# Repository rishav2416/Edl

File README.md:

# EDL Project of Group 10, Spring 2020-21
## PCB design
This repository contains all the files such as schematic, Board files needed to manufacture our pcb design. This PCB design is of a Temperature Controller Circuit which controls the temperature of a box in a said range with very less error

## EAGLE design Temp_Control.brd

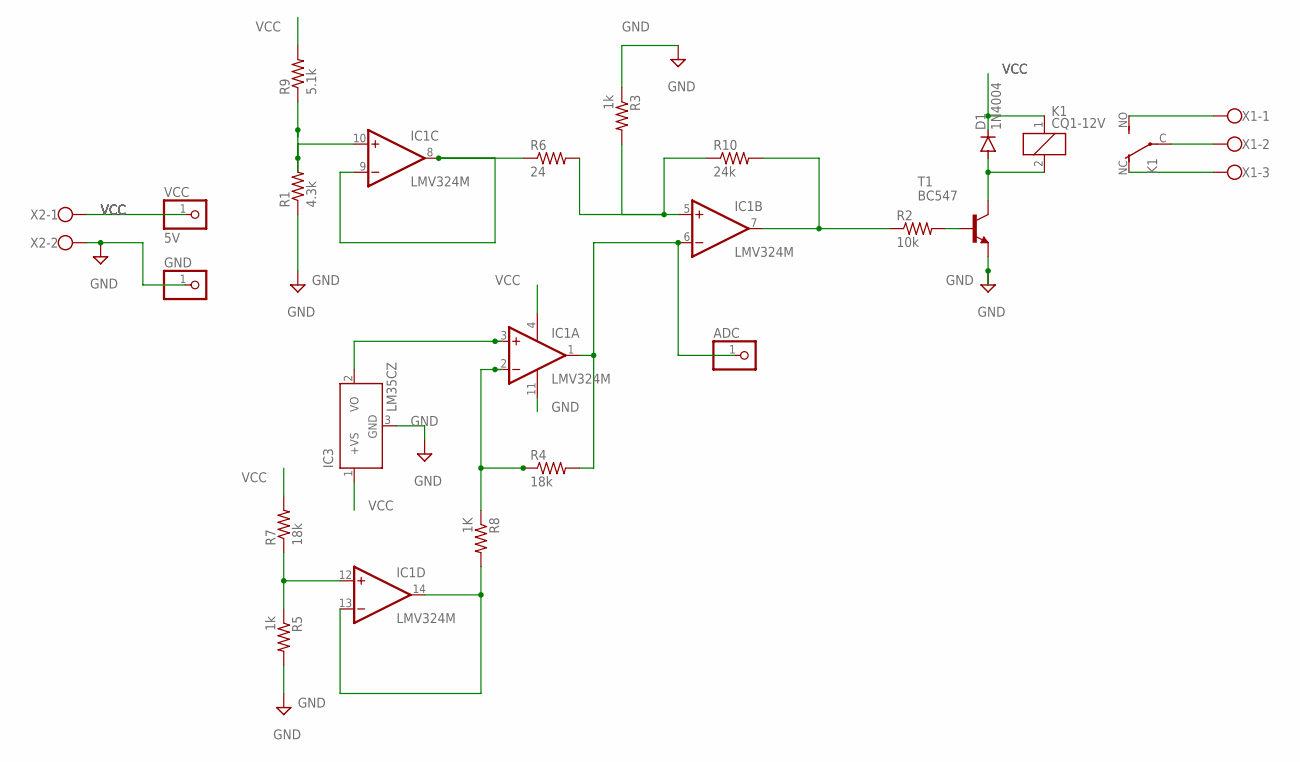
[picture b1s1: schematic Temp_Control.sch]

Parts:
ADC: PINHD-1X1; 1X01
D1: 1N4004; DO41-10
GND: PINHD-1X1; 1X01
IC1: LMV324M; SO14
IC3: LM35CZ; TO92
K1: CQ1-12V; CQ1
R1: 4.3k; 0207/10
R2: 10k; 0207/10
R3, R5: 1k; 0207/10
R4, R7: 18k; 0207/10
R6: 24; 0207/10
R8: 1K; 0207/10
R9: 5.1k; 0207/10
R10: 24k; 0207/10
T1: BC547; TO92
VCC: 5V; 1X01
X1: W237-103
X2: W237-102

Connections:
GND: GND.1, IC1.11 (V-), IC3.3 (GND), R1.1, R3.1, R5.2, T1.1 (E), X2.2
unnamed: IC1.3 (+IN), IC3.2 (VO)
unnamed: IC1.2 (-IN), R4.1, R8.1
unnamed: ADC.1, IC1.1 (OUT), IC1.6 (-IN), R4.2
unnamed: IC1.5 (+IN), R3.2, R6.2, R10.1
unnamed: IC1.7 (OUT), R2.1, R10.2
unnamed: IC1.10 (+IN), R1.2, R9.1
unnamed: IC1.8 (OUT), IC1.9 (-IN), R6.1
unnamed: IC1.13 (-IN), IC1.14 (OUT), R8.2
unnamed: R2.2, T1.2 (B)
unnamed: IC1.12 (+IN), R5.1, R7.1
unnamed: D1.A, K1.2, T1.3 (C)
unnamed: K1.NO (S), X1.1
unnamed: K1.C, X1.2
unnamed: K1.NC (O), X1.3
VCC: D1.C, IC1.4 (V+), IC3.1 (+VS), K1.1, R7.2, R9.2, VCC.1, X2.1

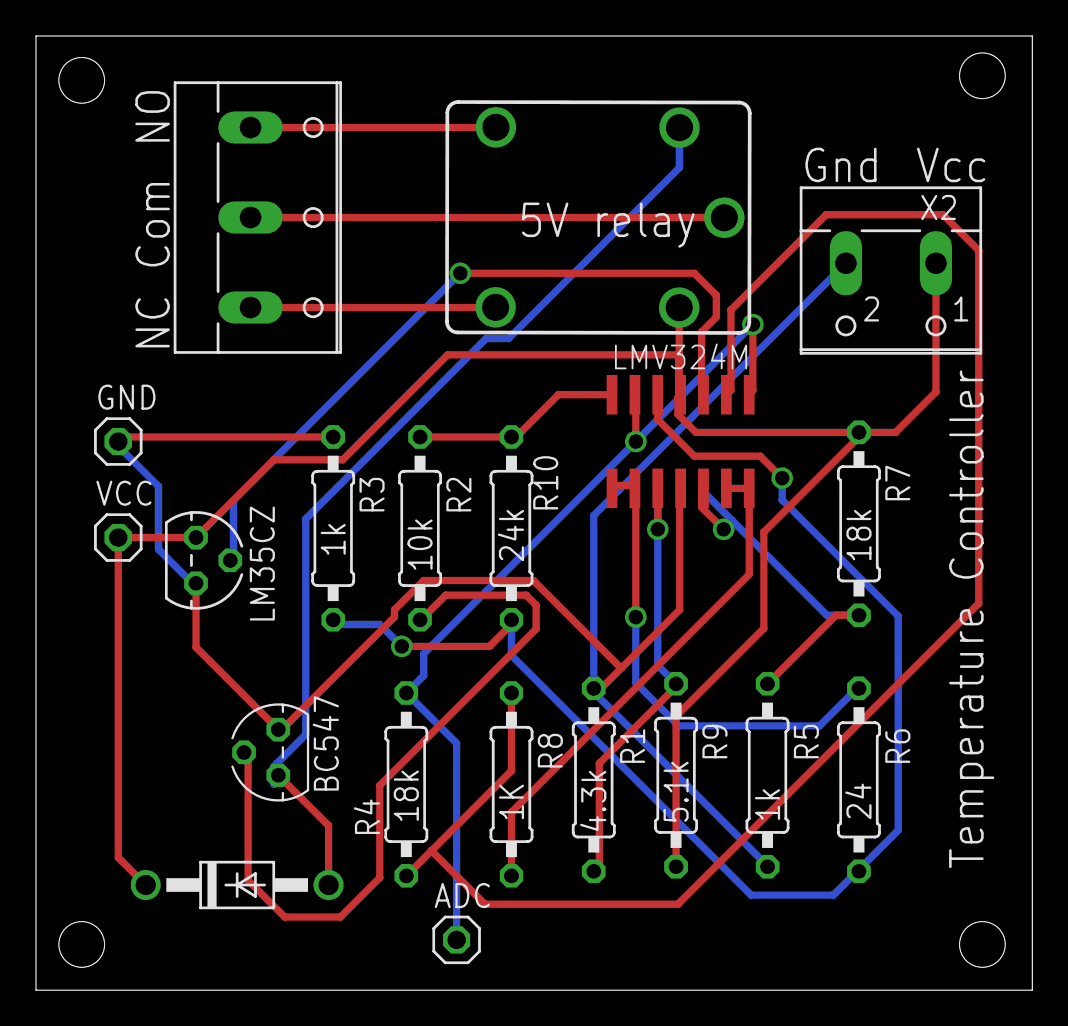
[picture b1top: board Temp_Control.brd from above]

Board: 2 copper layers, 55.4 x 53.0 mm, 20 parts (0 on the bottom side), 16 nets.

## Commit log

2021-04-15 Edl PCB Design of Project
